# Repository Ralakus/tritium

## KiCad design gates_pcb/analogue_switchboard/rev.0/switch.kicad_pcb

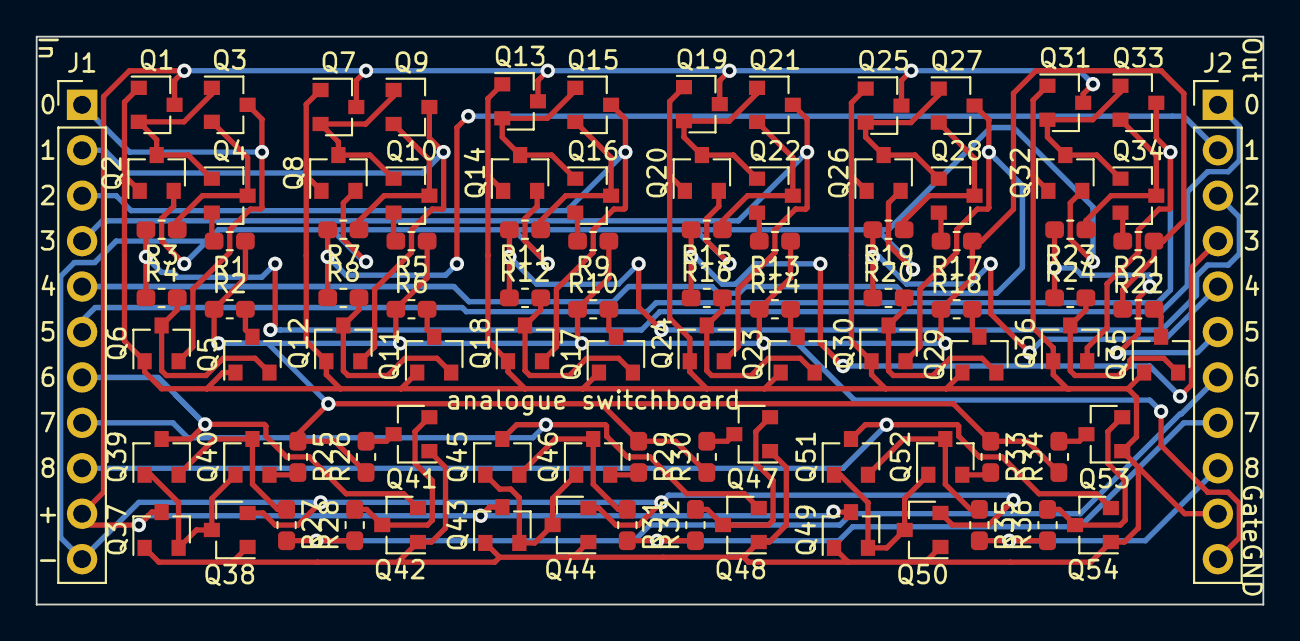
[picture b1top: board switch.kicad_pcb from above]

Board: 2 copper layers, 68.6 x 31.8 mm, 92 parts (0 on the bottom side), 67 nets.

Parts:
J1, J2: Conn_01x11; PinHeader_1x11_P2.54mm_Vertical
Q1, Q3, Q4, Q7, Q9, Q10, Q13, Q15, Q16, Q19, Q21, Q22, Q25, Q27, Q28, Q31, Q33, Q34, Q37, Q39, Q40, Q43, Q45, Q46, Q49, Q51, Q52: BSS84; SOT-23
Q2, Q5, Q6, Q8, Q11, Q12, Q14, Q17, Q18, Q20, Q23, Q24, Q26, Q29, Q30, Q32, Q35, Q36, Q38, Q41, Q42, Q44, Q47, Q48, Q50, Q53, Q54: 2N7002; SOT-23
R1, R2, R3, R4, R5, R6, R7, R8, R9, R10, R11, R12, R13, R14, R15, R16, R17, R18, R19, R20, R21, R22, R23, R24, R25, R26, R27, R28, R29, R30, R31, R32, R33, R34, R35, R36: 12k; R_0603_1608Metric_Pad1.05x0.95mm_HandSolder

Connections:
GND: J2.11, R1.1, R2.1, R5.1, R6.1, R9.1, R10.1, R13.1, R14.1, R17.1, R18.1, R21.1, R22.1, R25.1, R26.1, R29.1, R30.1, R33.1, R34.1
Gate: J2.10, Q1.1, Q2.1, Q5.1, Q6.1, Q7.1, Q8.1, Q11.1, Q12.1, Q13.1, Q14.1, Q17.1, Q18.1, Q19.1, Q20.1, Q23.1, Q24.1, Q25.1, Q26.1, Q29.1, Q30.1, Q31.1, Q32.1, Q35.1, Q36.1, Q37.1, Q38.1, Q41.1, Q42.1, Q43.1, Q44.1, Q47.1, Q48.1, Q49.1, Q50.1, Q53.1, Q54.1
I0: J1.1, Q3.3, Q6.2
I1: J1.2, Q9.3, Q12.2
I2: J1.3, Q15.3, Q18.2
I3: J1.4, Q21.3, Q24.2
I4: J1.5, Q27.3, Q30.2
I5: J1.6, Q33.3, Q36.2
I6: J1.7, Q39.3, Q42.2
I7: J1.8, Q45.3, Q48.2
I8: J1.9, Q51.3, Q54.2
unnamed: Q1.2, Q2.3, Q3.1, Q4.1
unnamed: Q3.2, Q4.3, R3.1
unnamed: Q4.2, R1.2
unnamed: Q5.2, Q6.3, R4.2
unnamed: Q5.3, R2.2
unnamed: Q7.2, Q8.3, Q9.1, Q10.1
unnamed: Q10.2, R5.2
unnamed: Q9.2, Q10.3, R7.1
unnamed: Q11.2, Q12.3, R8.2
unnamed: Q11.3, R6.2
unnamed: Q13.2, Q14.3, Q15.1, Q16.1
unnamed: Q15.2, Q16.3, R11.1
unnamed: Q16.2, R9.2
unnamed: Q17.2, Q18.3, R12.2
unnamed: Q17.3, R10.2
unnamed: Q19.2, Q20.3, Q21.1, Q22.1
unnamed: Q21.2, Q22.3, R15.1
unnamed: Q22.2, R13.2
unnamed: Q23.2, Q24.3, R16.2
unnamed: Q23.3, R14.2
unnamed: Q25.2, Q26.3, Q27.1, Q28.1
unnamed: Q27.2, Q28.3, R19.1
unnamed: Q28.2, R17.2
unnamed: Q29.2, Q30.3, R20.2
unnamed: Q29.3, R18.2
unnamed: Q31.2, Q32.3, Q33.1, Q34.1
unnamed: Q33.2, Q34.3, R23.1
unnamed: Q34.2, R21.2
unnamed: Q35.2, Q36.3, R24.2
unnamed: Q35.3, R22.2
unnamed: Q37.2, Q38.3, Q39.1, Q40.1
unnamed: Q39.2, Q40.3, R27.1
unnamed: Q40.2, R25.2
unnamed: Q41.2, Q42.3, R28.2
unnamed: Q41.3, R26.2
unnamed: Q43.2, Q44.3, Q45.1, Q46.1
unnamed: Q45.2, Q46.3, R31.1
unnamed: Q46.2, R29.2
unnamed: Q47.2, Q48.3, R32.2
unnamed: Q47.3, R30.2
unnamed: Q49.2, Q50.3, Q51.1, Q52.1
unnamed: Q51.2, Q52.3, R35.1
unnamed: Q52.2, R33.2
unnamed: Q53.2, Q54.3, R36.2
unnamed: Q53.3, R34.2
O0: J2.1, R3.2, R4.1
O1: J2.2, R7.2, R8.1
O2: J2.3, R11.2, R12.1
O3: J2.4, R15.2, R16.1
O4: J2.5, R19.2, R20.1
O5: J2.6, R23.2, R24.1
O6: J2.7, R27.2, R28.1
O7: J2.8, R31.2, R32.1
O8: J2.9, R35.2, R36.1
Vdd: J1.10, Q1.3, Q7.3, Q13.3, Q19.3, Q25.3, Q31.3, Q37.3, Q43.3, Q49.3
Vss: J1.11, Q2.2, Q8.2, Q14.2, Q20.2, Q26.2, Q32.2, Q38.2, Q44.2, Q50.2

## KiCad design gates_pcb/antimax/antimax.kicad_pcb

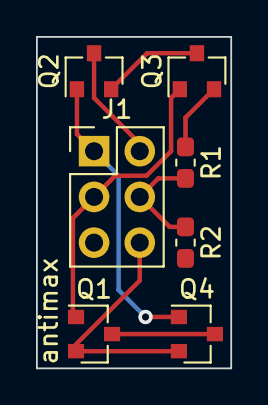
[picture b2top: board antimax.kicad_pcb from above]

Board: 2 copper layers, 10.8 x 18.4 mm, 7 parts (0 on the bottom side), 8 nets.

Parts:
J1: Conn_02x03_Odd_Even; PinHeader_2x03_P2.54mm_Vertical
Q1, Q4: 2N7002; SOT-23
Q2, Q3: BSS84; SOT-23
R1, R2: 12k; R_0603_1608Metric_Pad1.05x0.95mm_HandSolder

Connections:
A: J1.1, Q2.1, Q4.1
B: J1.3, Q1.1, Q3.1
unnamed: Q1.3, Q4.3, R2.2
unnamed: Q2.2, Q3.3
unnamed: Q3.2, R1.1
Out: J1.4, R1.2, R2.1
Vdd: J1.2, Q2.3
Vss: J1.6, Q1.2, Q4.2

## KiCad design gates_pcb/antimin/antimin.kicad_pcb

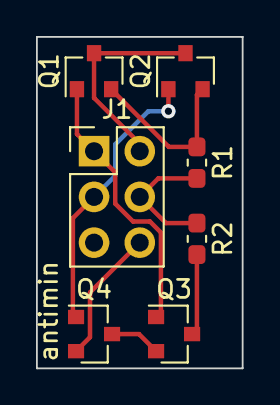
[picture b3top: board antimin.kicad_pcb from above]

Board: 2 copper layers, 11.4 x 18.4 mm, 7 parts (0 on the bottom side), 8 nets.

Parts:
J1: Conn_02x03_Odd_Even; PinHeader_2x03_P2.54mm_Vertical
Q1, Q2: BSS84; SOT-23
Q3, Q4: 2N7002E; SOT-23
R1, R2: 12k; R_0603_1608Metric_Pad1.05x0.95mm_HandSolder

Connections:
A: J1.1, Q1.1, Q3.1
B: J1.3, Q2.1, Q4.1
unnamed: Q1.2, Q2.2, R1.1
unnamed: Q3.2, Q4.3
unnamed: Q3.3, R2.2
Out: J1.4, R1.2, R2.1
Vdd: J1.2, Q1.3, Q2.3
Vss: J1.6, Q4.2

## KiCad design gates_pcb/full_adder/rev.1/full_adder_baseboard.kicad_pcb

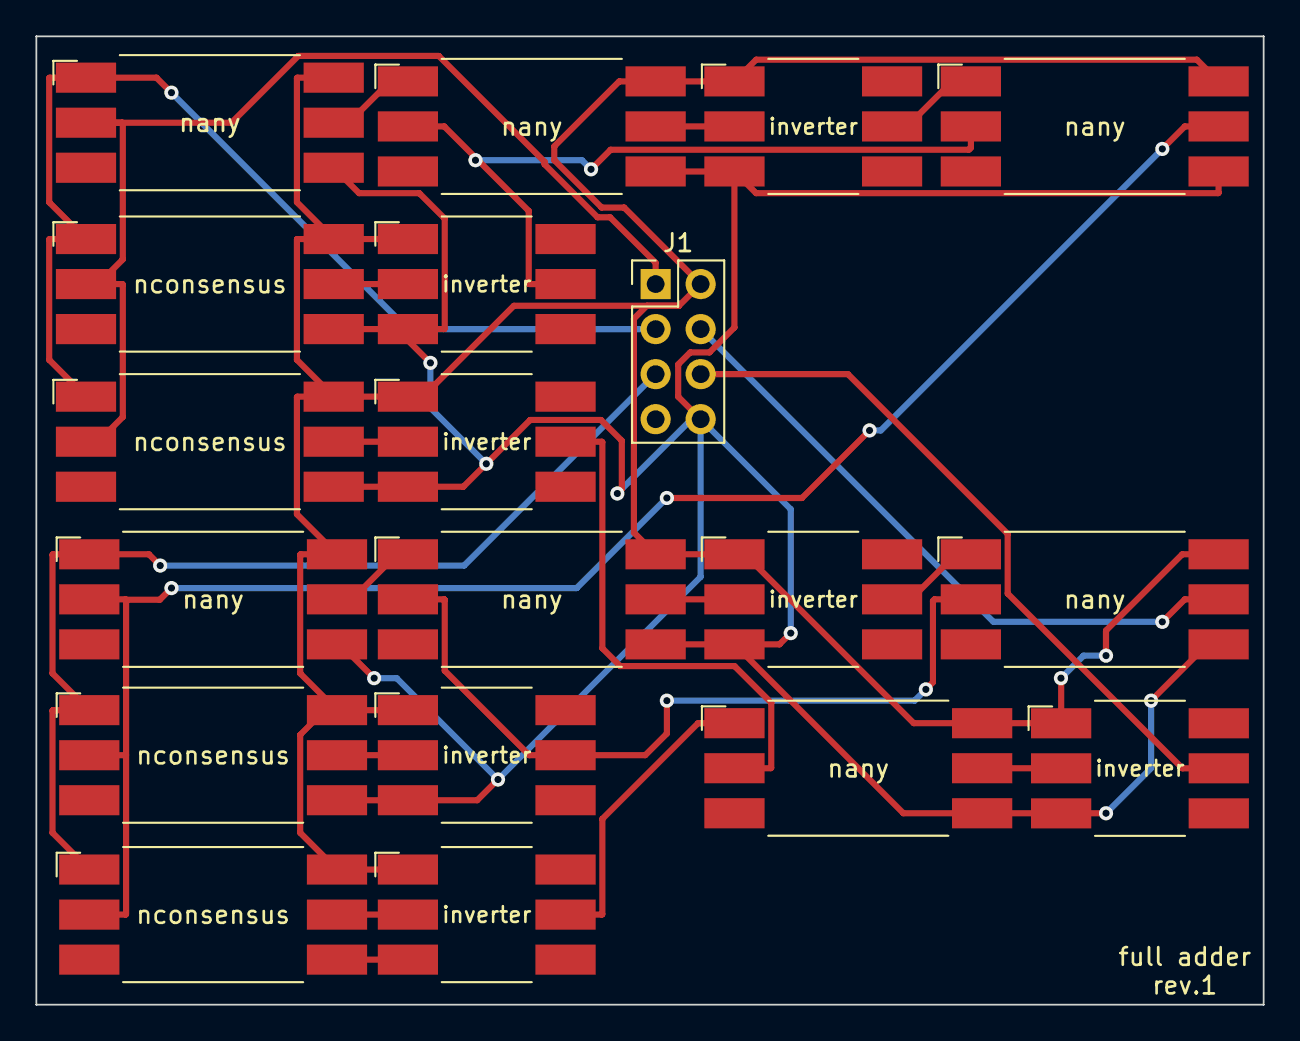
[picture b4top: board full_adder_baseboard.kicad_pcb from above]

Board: 2 copper layers, 69.2 x 54.6 mm, 19 parts (0 on the bottom side), 23 nets.

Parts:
A1, A6, A8, A9, A14, A15, A18: nany
A2, A3, A10, A11: nconsensus
A4, A5, A7, A12, A13, A16, A17: inverter
J1: Conn_02x04_Odd_Even; PinHeader_2x04_P2.54mm_Vertical

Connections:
A: A1.3, A2.3, A3.3, J1.1
B: A1.1, A2.1, A3.1, J1.3
C: A9.1, A10.1, A11.1, J1.5
Carry: A17.4, J1.6
unnamed: A1.4, A6.1
unnamed: A2.4, A4.3
unnamed: A3.4, A5.3
unnamed: A4.4, A6.3, A8.3
unnamed: A6.4, A7.3
unnamed: A7.4, A8.1
unnamed: A8.4, A9.3, A10.3, A11.3
unnamed: A10.4, A12.3
unnamed: A11.4, A13.3
unnamed: A12.4, A14.3, A18.3
unnamed: A13.4, A15.1
unnamed: A9.4, A14.1
unnamed: A14.4, A16.3
unnamed: A5.4, A15.3
unnamed: A15.4, A17.3
unnamed: A16.4, A18.1
Sum: A18.4, J1.4
Vdd: A1.2, A2.2, A3.2, A4.1, A5.1, A6.2, A7.1, A8.2, A9.2, A10.2, A11.2, A12.1, A13.1, A14.2, A15.2, A16.1, A17.1, A18.2, J1.2
Vss: A1.6, A2.6, A3.6, A4.5, A5.5, A6.6, A7.5, A8.6, A9.6, A10.6, A11.6, A12.5, A13.5, A14.6, A15.6, A16.5, A17.5, A18.6, J1.8

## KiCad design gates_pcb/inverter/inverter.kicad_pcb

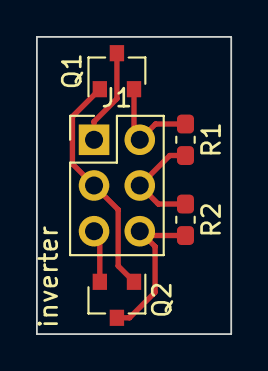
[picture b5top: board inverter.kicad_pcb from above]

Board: 2 copper layers, 10.8 x 16.5 mm, 5 parts (0 on the bottom side), 6 nets.

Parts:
J1: Conn_02x03_Odd_Even; PinHeader_2x03_P2.54mm_Vertical
Q1: BSS84; SOT-23
Q2: 2N7002; SOT-23
R1, R2: 12k; R_0603_1608Metric_Pad1.05x0.95mm_HandSolder

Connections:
In: J1.3, Q1.1, Q2.1
Nti: J1.6, Q2.3, R2.2
Out: J1.4, R1.2, R2.1
Pti: J1.2, Q1.2, R1.1
Vdd: J1.1, Q1.3
Vss: J1.5, Q2.2
